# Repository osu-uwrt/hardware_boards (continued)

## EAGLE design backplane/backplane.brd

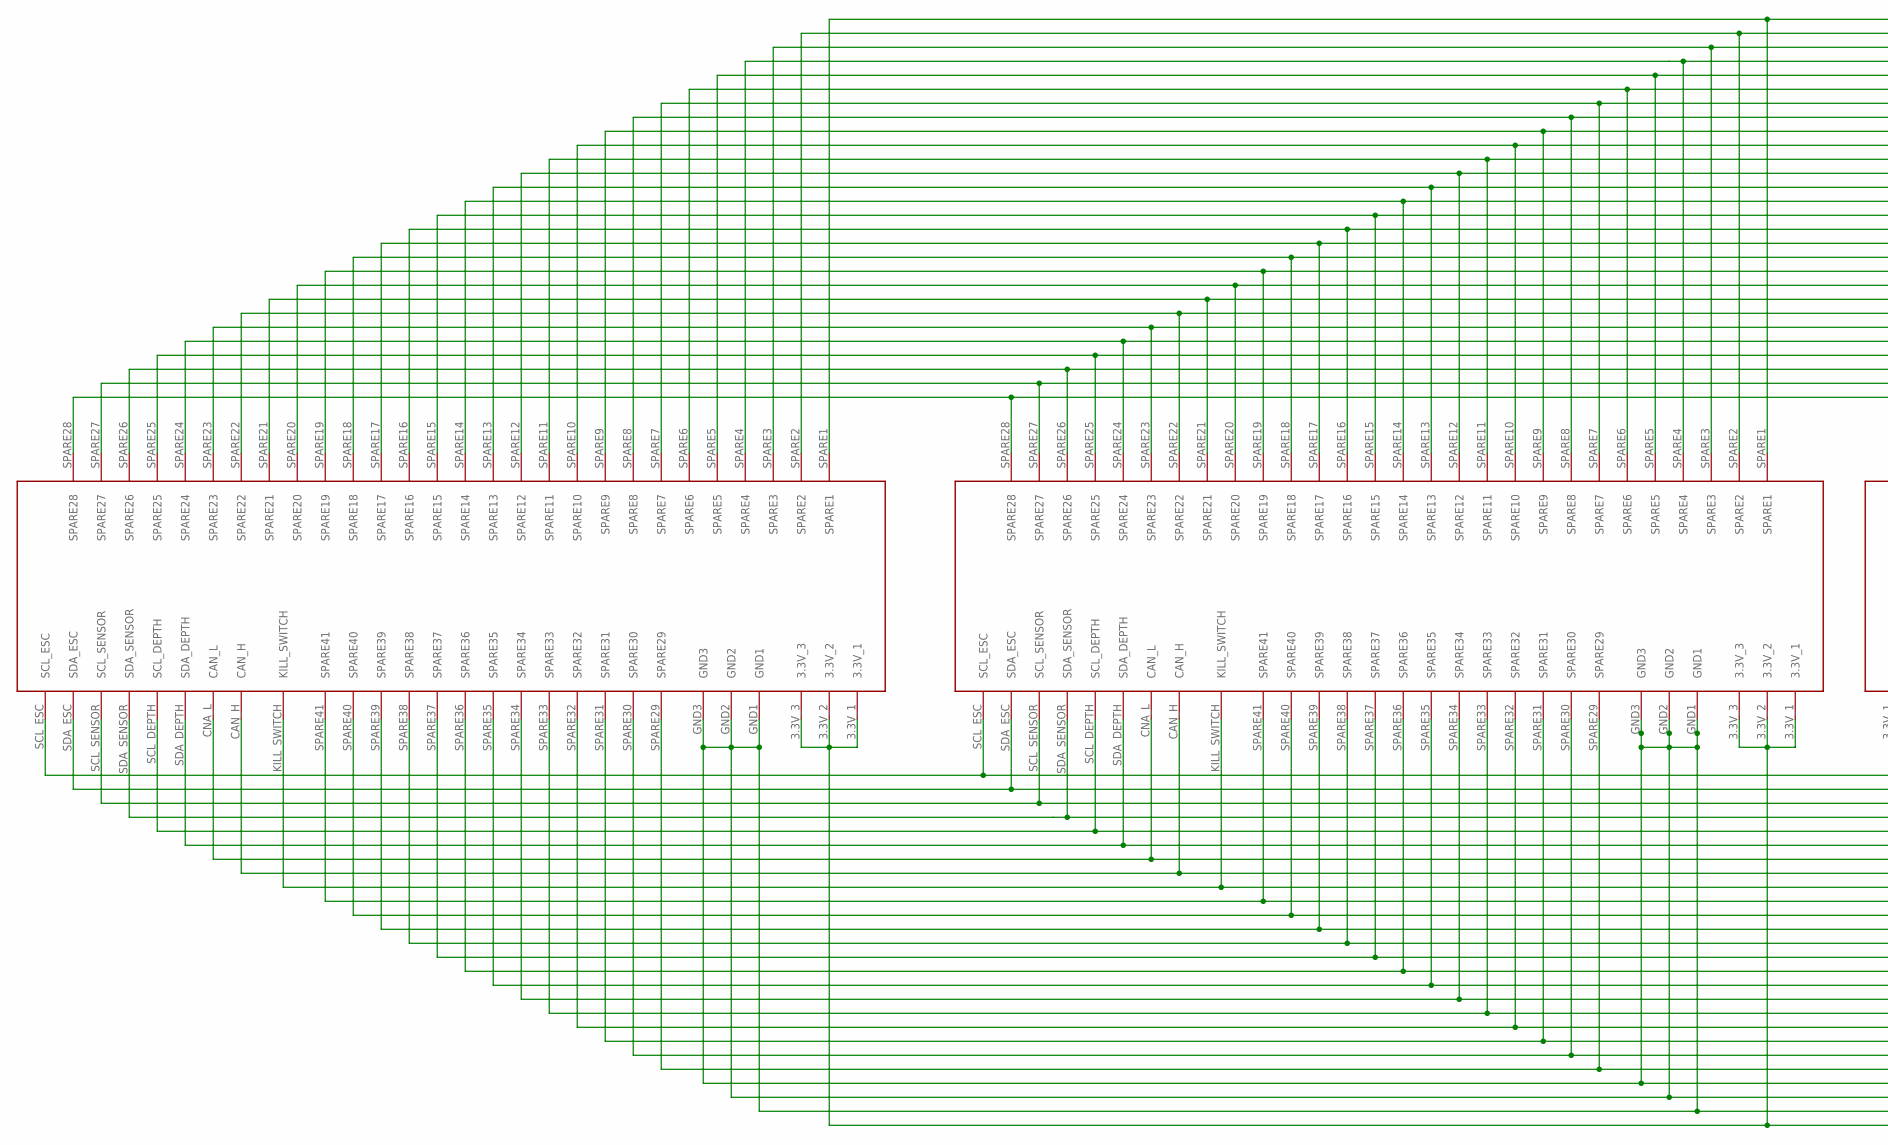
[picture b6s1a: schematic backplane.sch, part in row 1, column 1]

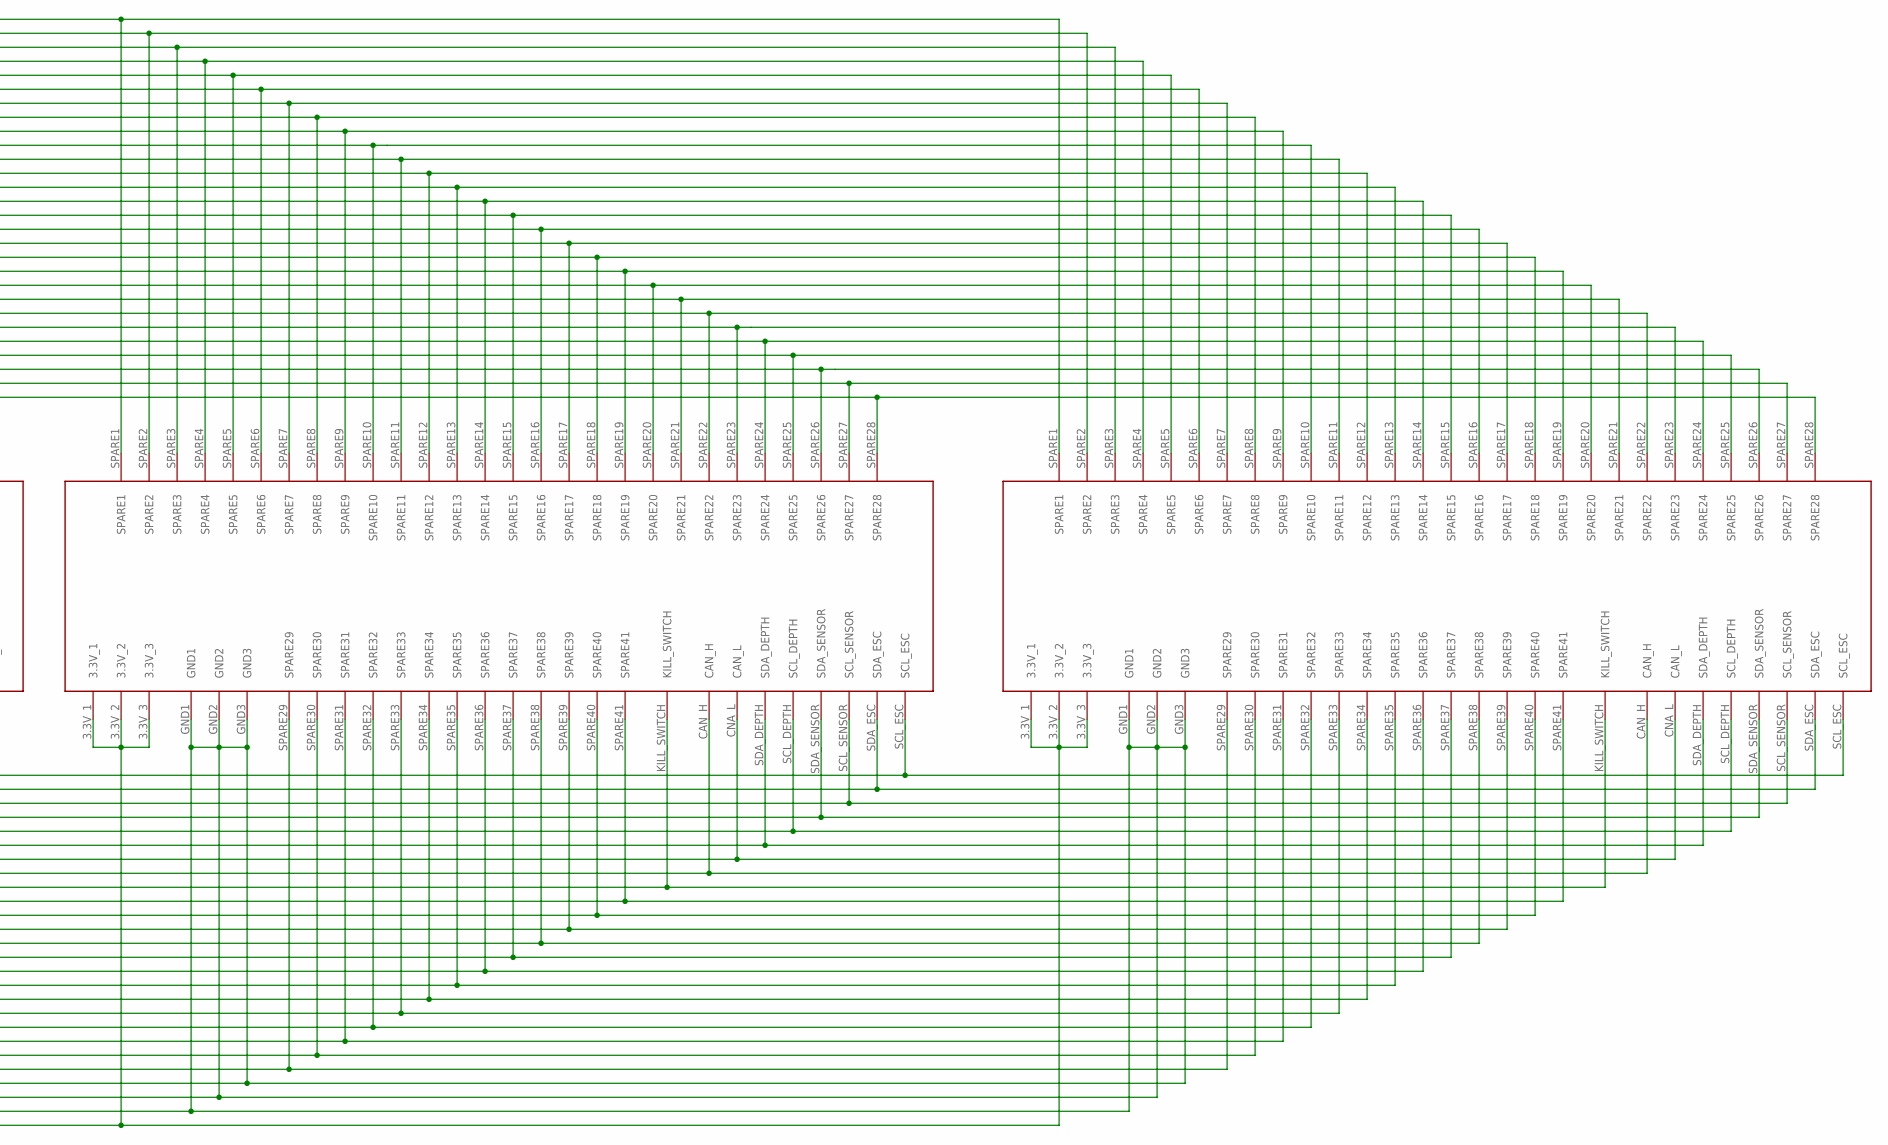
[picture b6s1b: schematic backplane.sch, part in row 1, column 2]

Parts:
CO-PROCESSOR: 5530843_MATE; 5530843-6-BACKPLANEMATE
CONVERTER: 5530843_MATE; 5530843-6-BACKPLANEMATE
EXTRA: 5530843_MATE; 5530843-6-BACKPLANEMATE
LOAD_BALANCER: 5530843_MATE; 5530843-6-BACKPLANEMATE

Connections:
3.3: CO-PROCESSOR.3.3V_1, CO-PROCESSOR.3.3V_2, CO-PROCESSOR.3.3V_3, CO-PROCESSOR.SPARE1, CO-PROCESSOR.SPARE2, CO-PROCESSOR.SPARE3, CONVERTER.3.3V_1, CONVERTER.3.3V_2, CONVERTER.3.3V_3, CONVERTER.SPARE1, CONVERTER.SPARE2, CONVERTER.SPARE3, EXTRA.3.3V_1, EXTRA.3.3V_2, EXTRA.3.3V_3, EXTRA.SPARE1, EXTRA.SPARE2, EXTRA.SPARE3, LOAD_BALANCER.3.3V_1, LOAD_BALANCER.3.3V_2, LOAD_BALANCER.3.3V_3, LOAD_BALANCER.SPARE1, LOAD_BALANCER.SPARE2, LOAD_BALANCER.SPARE3
CAN_H: CO-PROCESSOR.CAN_H, CONVERTER.CAN_H, EXTRA.CAN_H, LOAD_BALANCER.CAN_H
CAN_L: CO-PROCESSOR.CNA_L (CAN_L), CONVERTER.CNA_L (CAN_L), EXTRA.CNA_L (CAN_L), LOAD_BALANCER.CNA_L (CAN_L)
GND: CO-PROCESSOR.GND1, CO-PROCESSOR.GND2, CO-PROCESSOR.GND3, CO-PROCESSOR.SPARE4, CO-PROCESSOR.SPARE5, CO-PROCESSOR.SPARE6, CONVERTER.GND1, CONVERTER.GND2, CONVERTER.GND3, CONVERTER.SPARE4, CONVERTER.SPARE5, CONVERTER.SPARE6, EXTRA.GND1, EXTRA.GND2, EXTRA.GND3, EXTRA.SPARE4, EXTRA.SPARE5, EXTRA.SPARE6, LOAD_BALANCER.GND1, LOAD_BALANCER.GND2, LOAD_BALANCER.GND3, LOAD_BALANCER.SPARE4, LOAD_BALANCER.SPARE5, LOAD_BALANCER.SPARE6
KILL_SWITCH: CO-PROCESSOR.KILL_SWITCH, CONVERTER.KILL_SWITCH, EXTRA.KILL_SWITCH, LOAD_BALANCER.KILL_SWITCH
SCL_DEPTH: CO-PROCESSOR.SCL_DEPTH, CONVERTER.SCL_DEPTH, EXTRA.SCL_DEPTH, LOAD_BALANCER.SCL_DEPTH
SCL_ESC: CO-PROCESSOR.SCL_ESC, CONVERTER.SCL_ESC, EXTRA.SCL_ESC, LOAD_BALANCER.SCL_ESC
SCL_SENSOR: CO-PROCESSOR.SCL_SENSOR, CONVERTER.SCL_SENSOR, EXTRA.SCL_SENSOR, LOAD_BALANCER.SCL_SENSOR
SDA_DEPTH: CO-PROCESSOR.SDA_DEPTH, CONVERTER.SDA_DEPTH, EXTRA.SDA_DEPTH, LOAD_BALANCER.SDA_DEPTH
SDA_ESC: CO-PROCESSOR.SDA_ESC, CONVERTER.SDA_ESC, EXTRA.SDA_ESC, LOAD_BALANCER.SDA_ESC
SDA_SENSOR: CO-PROCESSOR.SDA_SENSOR, CONVERTER.SDA_SENSOR, EXTRA.SDA_SENSOR, LOAD_BALANCER.SDA_SENSOR
SPARE7: CO-PROCESSOR.SPARE7, CONVERTER.SPARE7, EXTRA.SPARE7, LOAD_BALANCER.SPARE7
SPARE8: CO-PROCESSOR.SPARE8, CONVERTER.SPARE8, EXTRA.SPARE8, LOAD_BALANCER.SPARE8
SPARE9: CO-PROCESSOR.SPARE9, CONVERTER.SPARE9, EXTRA.SPARE9, LOAD_BALANCER.SPARE9
SPARE10: CO-PROCESSOR.SPARE10, CONVERTER.SPARE10, EXTRA.SPARE10, LOAD_BALANCER.SPARE10
SPARE11: CO-PROCESSOR.SPARE11, CONVERTER.SPARE11, EXTRA.SPARE11, LOAD_BALANCER.SPARE11
SPARE12: CO-PROCESSOR.SPARE12, CONVERTER.SPARE12, EXTRA.SPARE12, LOAD_BALANCER.SPARE12
SPARE13: CO-PROCESSOR.SPARE13, CONVERTER.SPARE13, EXTRA.SPARE13, LOAD_BALANCER.SPARE13
SPARE14: CO-PROCESSOR.SPARE14, CONVERTER.SPARE14, EXTRA.SPARE14, LOAD_BALANCER.SPARE14
SPARE15: CO-PROCESSOR.SPARE15, CONVERTER.SPARE15, EXTRA.SPARE15, LOAD_BALANCER.SPARE15
SPARE16: CO-PROCESSOR.SPARE16, CONVERTER.SPARE16, EXTRA.SPARE16, LOAD_BALANCER.SPARE16
SPARE17: CO-PROCESSOR.SPARE17, CONVERTER.SPARE17, EXTRA.SPARE17, LOAD_BALANCER.SPARE17
SPARE18: CO-PROCESSOR.SPARE18, CONVERTER.SPARE18, EXTRA.SPARE18, LOAD_BALANCER.SPARE18
SPARE19: CO-PROCESSOR.SPARE19, CONVERTER.SPARE19, EXTRA.SPARE19, LOAD_BALANCER.SPARE19
SPARE20: CO-PROCESSOR.SPARE20, CONVERTER.SPARE20, EXTRA.SPARE20, LOAD_BALANCER.SPARE20
SPARE21: CO-PROCESSOR.SPARE21, CONVERTER.SPARE21, EXTRA.SPARE21, LOAD_BALANCER.SPARE21
SPARE22: CO-PROCESSOR.SPARE22, CONVERTER.SPARE22, EXTRA.SPARE22, LOAD_BALANCER.SPARE22
SPARE23: CO-PROCESSOR.SPARE23, CONVERTER.SPARE23, EXTRA.SPARE23, LOAD_BALANCER.SPARE23
SPARE24: CO-PROCESSOR.SPARE24, CONVERTER.SPARE24, EXTRA.SPARE24, LOAD_BALANCER.SPARE24
SPARE25: CO-PROCESSOR.SPARE25, CONVERTER.SPARE25, EXTRA.SPARE25, LOAD_BALANCER.SPARE25
SPARE26: CO-PROCESSOR.SPARE26, CONVERTER.SPARE26, EXTRA.SPARE26, LOAD_BALANCER.SPARE26
SPARE27: CO-PROCESSOR.SPARE27, CONVERTER.SPARE27, EXTRA.SPARE27, LOAD_BALANCER.SPARE27
SPARE28: CO-PROCESSOR.SPARE28, CONVERTER.SPARE28, EXTRA.SPARE28, LOAD_BALANCER.SPARE28
SPARE29: CO-PROCESSOR.SPARE29, CONVERTER.SPARE29, EXTRA.SPARE29, LOAD_BALANCER.SPARE29
SPARE30: CO-PROCESSOR.SPARE30, CONVERTER.SPARE30, EXTRA.SPARE30, LOAD_BALANCER.SPARE30
SPARE31: CO-PROCESSOR.SPARE31, CONVERTER.SPARE31, EXTRA.SPARE31, LOAD_BALANCER.SPARE31
SPARE32: CO-PROCESSOR.SPARE32, CONVERTER.SPARE32, EXTRA.SPARE32, LOAD_BALANCER.SPARE32
SPARE33: CO-PROCESSOR.SPARE33, CONVERTER.SPARE33, EXTRA.SPARE33, LOAD_BALANCER.SPARE33
SPARE34: CO-PROCESSOR.SPARE34, CONVERTER.SPARE34, EXTRA.SPARE34, LOAD_BALANCER.SPARE34
SPARE35: CO-PROCESSOR.SPARE35, CONVERTER.SPARE35, EXTRA.SPARE35, LOAD_BALANCER.SPARE35
SPARE36: CO-PROCESSOR.SPARE36, CONVERTER.SPARE36, EXTRA.SPARE36, LOAD_BALANCER.SPARE36
SPARE37: CO-PROCESSOR.SPARE37, CONVERTER.SPARE37, EXTRA.SPARE37, LOAD_BALANCER.SPARE37
SPARE38: CO-PROCESSOR.SPARE38, CONVERTER.SPARE38, EXTRA.SPARE38, LOAD_BALANCER.SPARE38
SPARE39: CO-PROCESSOR.SPARE39, CONVERTER.SPARE39, EXTRA.SPARE39, LOAD_BALANCER.SPARE39
SPARE40: CO-PROCESSOR.SPARE40, CONVERTER.SPARE40, EXTRA.SPARE40, LOAD_BALANCER.SPARE40
SPARE41: CO-PROCESSOR.SPARE41, CONVERTER.SPARE41, EXTRA.SPARE41, LOAD_BALANCER.SPARE41

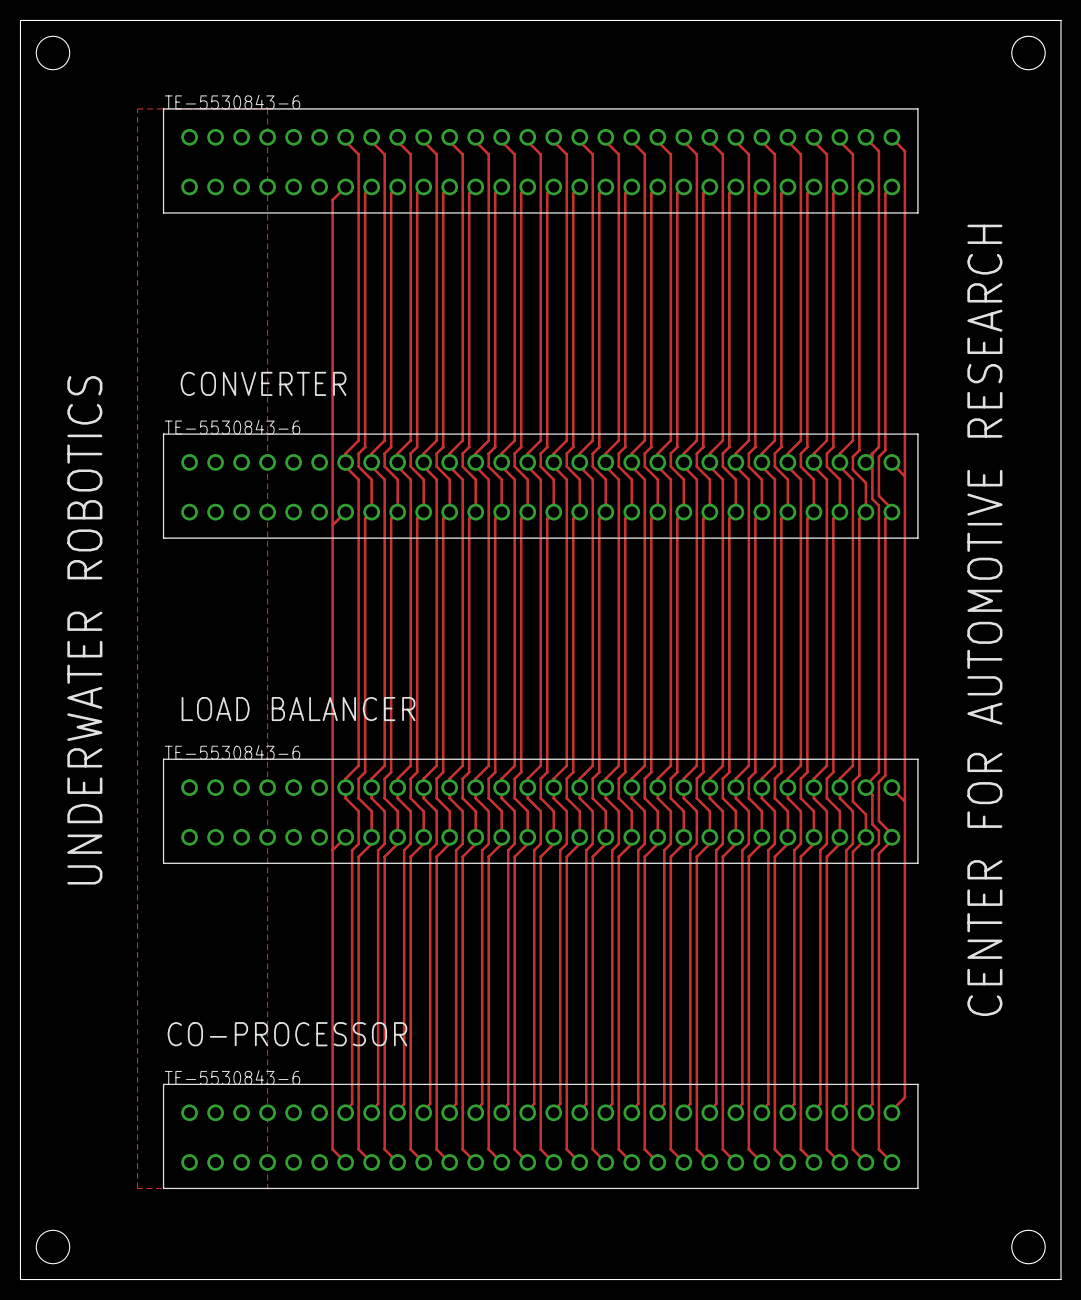
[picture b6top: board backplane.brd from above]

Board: 2 copper layers, 101.6 x 122.9 mm, 4 parts (0 on the bottom side), 46 nets.

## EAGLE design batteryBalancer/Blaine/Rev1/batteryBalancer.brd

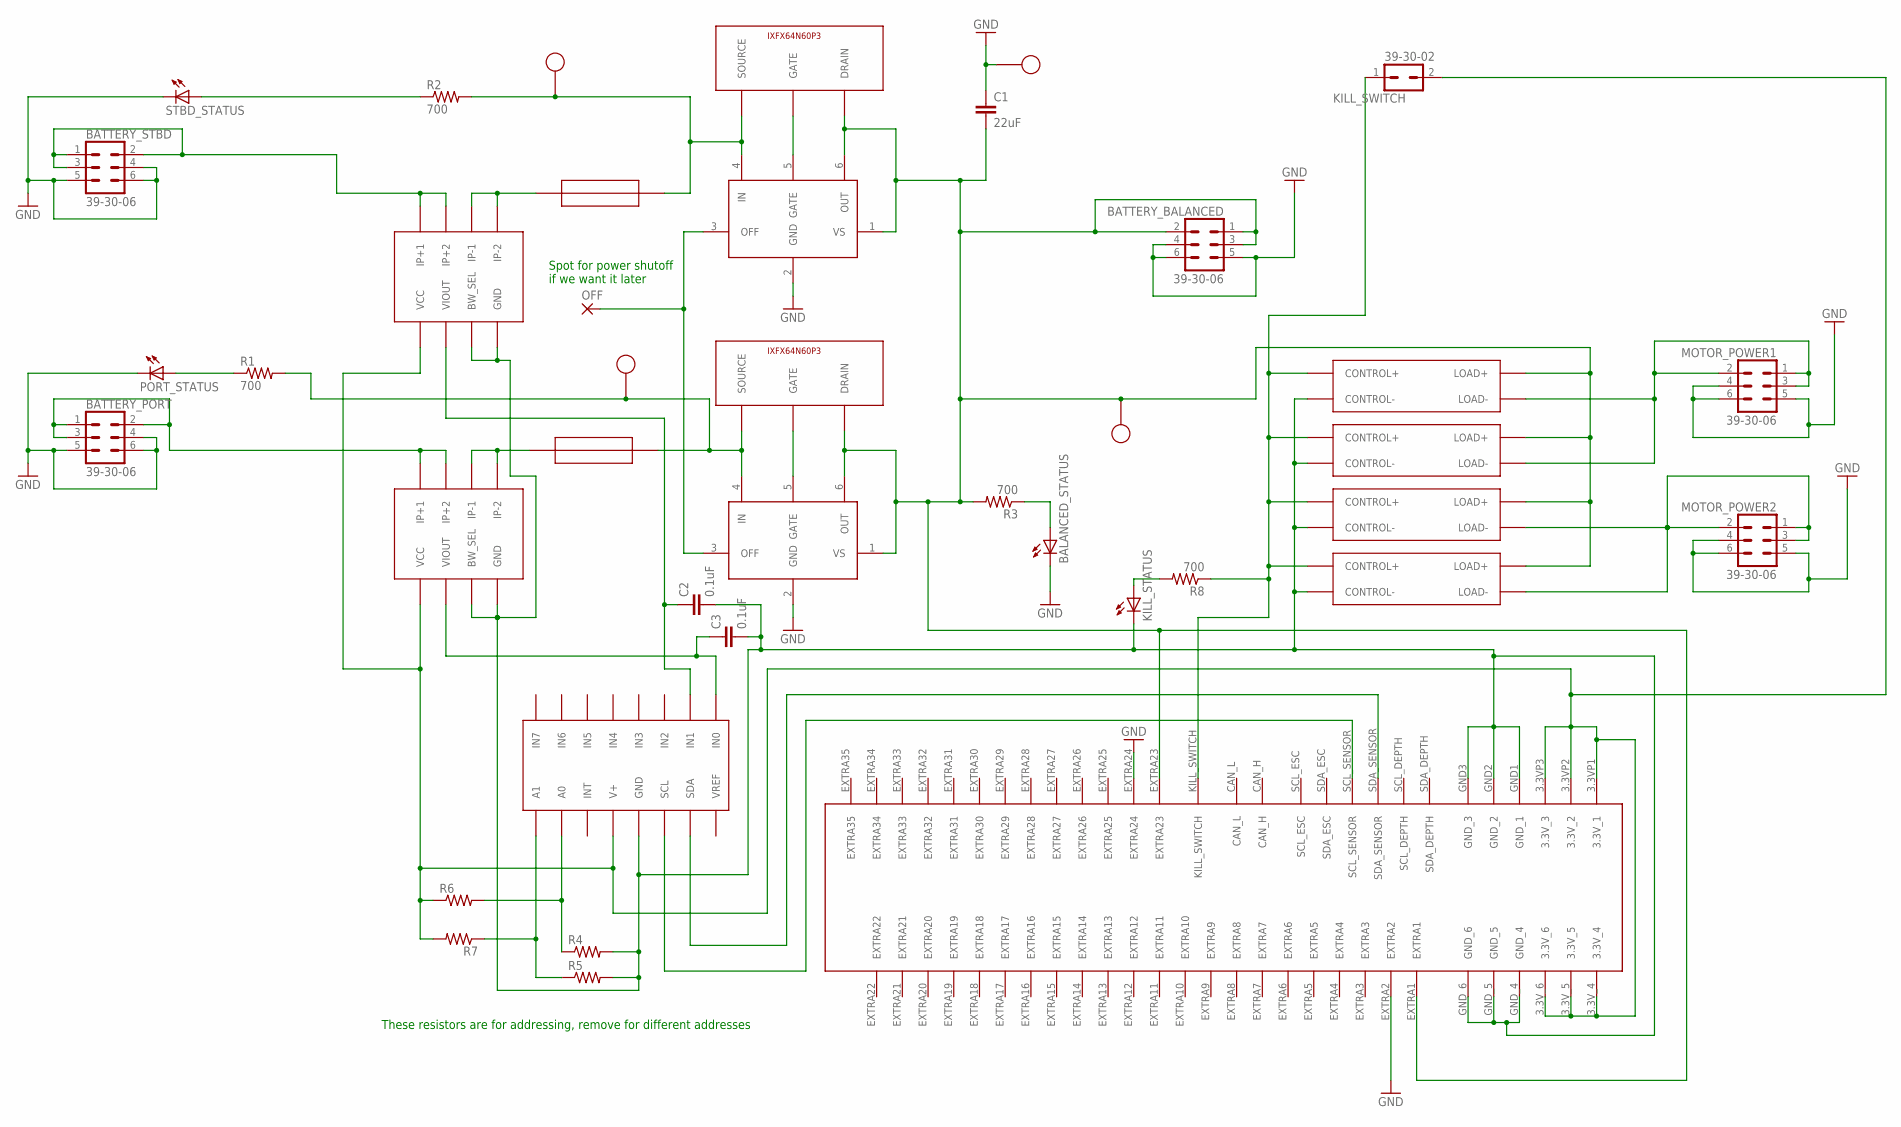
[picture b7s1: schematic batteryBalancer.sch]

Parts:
ADC: ADC128D818; TSSOP-16
BALANCED_STATUS: LTST-S270GKT
BATTERY_BALANCED: 39-30-06; 39-30-?06?
BATTERY_PORT: 39-30-06; 39-30-?06?
BATTERY_STBD: 39-30-06; 39-30-?06?
C1: 22uF; CAP-PTH-SMALL-KIT
C2, C3: 0.1uF; CAP-PTH-SMALL-KIT
EDGE_CONNECTOR: 5530843; 5530843-6-BOARDFINGERS
KILL_STATUS: LTST-S270GKT
KILL_SWITCH: 39-30-02; 39-30-?02?
MOTOR_POWER1, MOTOR_POWER2: 39-30-06; 39-30-?06?
OFF: 2,54/1,1
PORT_CS: ACS722; SOIC-8
PORT_FC: LM5050-1; SOT23-6
PORT_FET: IXFX64N60P3
PORT_FUSE: 01220083Z
PORT_STATUS: LTST-S270GKT
R1, R2, R3, R8: 700; 0207/7
R4, R5, R6, R7: R-US_0204/5; 0204/5
RELAY2, RELAY3, RELAY4: CMX60D20
RLAY1: CMX60D20
STBD_CS: ACS722; SOIC-8
STBD_FC: LM5050-1; SOT23-6
STBD_FET: IXFX64N60P3
STBD_FUSE: 01220083Z
STBD_STATUS: LTST-S270GKT
U$1, U$2, U$3, U$4: 5010_C

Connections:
3.3V: ADC.V+, EDGE_CONNECTOR.3.3VP1 (3.3V_1), EDGE_CONNECTOR.3.3VP2 (3.3V_2), EDGE_CONNECTOR.3.3VP3 (3.3V_3), EDGE_CONNECTOR.3.3V_4, EDGE_CONNECTOR.3.3V_5, EDGE_CONNECTOR.3.3V_6, KILL_SWITCH.2, PORT_CS.VCC, R6.1, R7.2, STBD_CS.VCC
ADC_A0: ADC.A0, R4.1, R6.2
ADC_A1: ADC.A1, R5.1, R7.1
BALANCED_INDICATOR: BALANCED_STATUS.ANODE (A), R3.1
BALANCED_POWER: BATTERY_BALANCED.1, BATTERY_BALANCED.2, BATTERY_BALANCED.3, C1.2, EDGE_CONNECTOR.EXTRA1, EDGE_CONNECTOR.EXTRA23, PORT_FC.1 (VS), PORT_FC.6 (OUT), PORT_FET.DRAIN, R3.2, RELAY2.LOAD+, RELAY3.LOAD+, RELAY4.LOAD+, RLAY1.LOAD+, STBD_FC.1 (VS), STBD_FC.6 (OUT), STBD_FET.DRAIN, U$3.P$1
GND: BALANCED_STATUS.CATHODE (C), BATTERY_BALANCED.4, BATTERY_BALANCED.5, BATTERY_BALANCED.6, BATTERY_PORT.4, BATTERY_PORT.5, BATTERY_PORT.6, BATTERY_STBD.4, BATTERY_STBD.5, BATTERY_STBD.6, C1.1, EDGE_CONNECTOR.EXTRA2, EDGE_CONNECTOR.EXTRA24, MOTOR_POWER1.4, MOTOR_POWER1.5, MOTOR_POWER1.6, MOTOR_POWER2.4, MOTOR_POWER2.5, MOTOR_POWER2.6, PORT_FC.2 (GND), PORT_STATUS.CATHODE (C), STBD_FC.2 (GND), STBD_STATUS.CATHODE (C), U$4.P$1
KILL_SWITCH: EDGE_CONNECTOR.KILL_SWITCH, KILL_SWITCH.1, R8.1, RELAY2.CONTROL+, RELAY3.CONTROL+, RELAY4.CONTROL+, RLAY1.CONTROL+
LOGIC_GND: ADC.GND, C2.2, C3.2, EDGE_CONNECTOR.GND1 (GND_1), EDGE_CONNECTOR.GND2 (GND_2), EDGE_CONNECTOR.GND3 (GND_3), EDGE_CONNECTOR.GND_4, EDGE_CONNECTOR.GND_5, EDGE_CONNECTOR.GND_6, KILL_STATUS.CATHODE (C), PORT_CS.BW_SEL, PORT_CS.GND, R4.2, R5.2, RELAY2.CONTROL-, RELAY3.CONTROL-, RELAY4.CONTROL-, RLAY1.CONTROL-, STBD_CS.BW_SEL, STBD_CS.GND
MOTOR_POWER1: MOTOR_POWER1.1, MOTOR_POWER1.2, MOTOR_POWER1.3, RELAY2.LOAD-, RLAY1.LOAD-
MOTOR_POWER2: MOTOR_POWER2.1, MOTOR_POWER2.2, MOTOR_POWER2.3, RELAY3.LOAD-, RELAY4.LOAD-
unnamed: STBD_CS.IP-1, STBD_CS.IP-2, STBD_FUSE.P$1, STBD_FUSE.P$2
unnamed: KILL_STATUS.ANODE (A), R8.2
OFF: OFF.1, PORT_FC.3 (OFF), STBD_FC.3 (OFF)
PORT_CURRENT: ADC.IN0, C3.1, PORT_CS.VIOUT
PORT_GATE: PORT_FC.5 (GATE), PORT_FET.GATE
PORT_POWER: BATTERY_PORT.1, BATTERY_PORT.2, BATTERY_PORT.3, PORT_CS.IP+1, PORT_CS.IP+2
PORT_SOURCE: PORT_FC.4 (IN), PORT_FET.SOURCE, PORT_FUSE.P$3, PORT_FUSE.P$4, R1.2, U$2.P$1
PORT_STATUS: PORT_STATUS.ANODE (A), R1.1
PORT_UNBALANCED: PORT_CS.IP-1, PORT_CS.IP-2, PORT_FUSE.P$1, PORT_FUSE.P$2
SCL: ADC.SCL, EDGE_CONNECTOR.SCL_SENSOR
SDA: ADC.SDA, EDGE_CONNECTOR.SDA_SENSOR
STBD_CURRENT: ADC.IN1, C2.1, STBD_CS.VIOUT
STBD_GATE: STBD_FC.5 (GATE), STBD_FET.GATE
STBD_POWER: BATTERY_STBD.1, BATTERY_STBD.2, BATTERY_STBD.3, STBD_CS.IP+1, STBD_CS.IP+2
STBD_STATUS: R2.1, STBD_STATUS.ANODE (A)
STBD_UNBALANCED: R2.2, STBD_FC.4 (IN), STBD_FET.SOURCE, STBD_FUSE.P$3, STBD_FUSE.P$4, U$1.P$1

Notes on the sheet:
These resistors are for addressing, remove for different addresses
Spot for power shutoff if we want it later

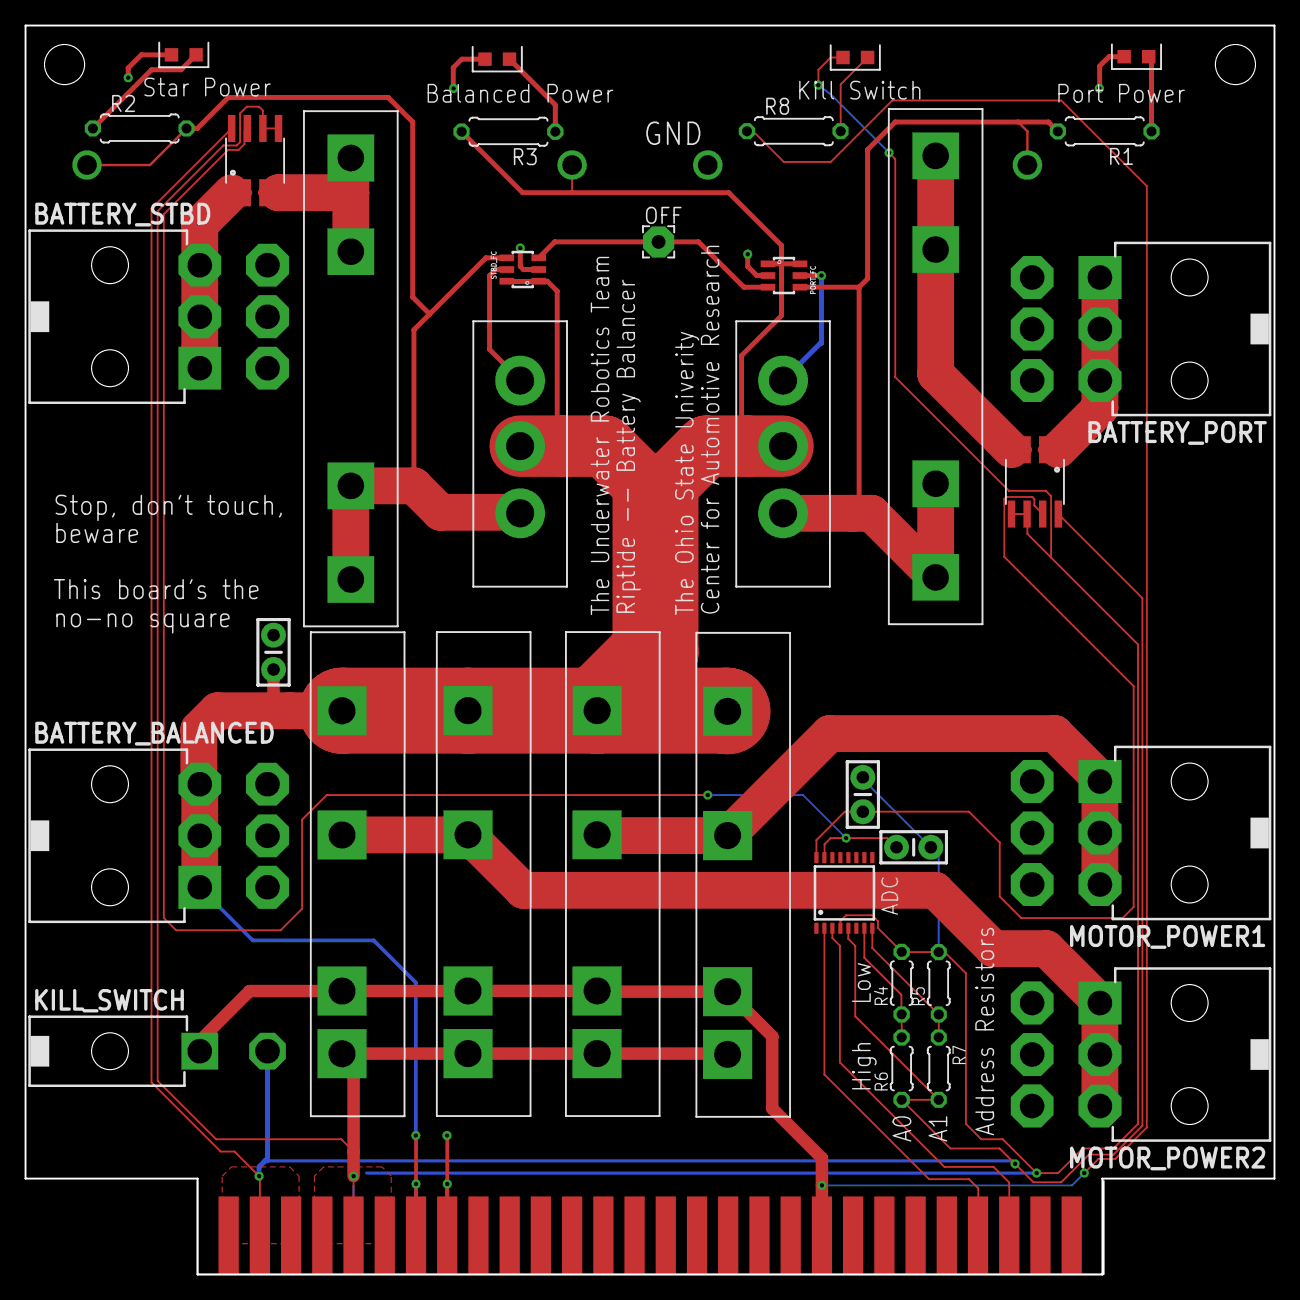
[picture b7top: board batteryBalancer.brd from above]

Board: 2 copper layers, 101.6 x 101.6 mm, 40 parts (0 on the bottom side), 26 nets.
